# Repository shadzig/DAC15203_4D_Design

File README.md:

# DAC15203: 4D Design

## Virtual pet (Egg)

**Name:** Michail Dzigajev

**Student No:** 96410016

**Course:** BA (Hons) Design & Coding, Level 2.

**Unit Code:** DAC15203

### **Introduction**
Welcome the pet README file. This is an instruction manual on how to start up the pet demo, due to the main scrip currently not being fully functional, and instead I'm showing the visual features of the pet within the demo version that cycles through the sleep mode times and allows you to press the button to reset itself to the smile animation state.

### **Instructions**

##### **Here is how to start up the pet Demo mode**
1. Unfortunately you will have to take off both the top shells of the pet by lightly pulling them away from the base. This is due to me having under-voting issues with the Lithium battery that is in place at the entry of the 3D base hole, so the Pi is no longer powered by the battery temporarily.  I had to remove the wires that connect the battery and Pi while the issue is being resolved, in addition to there being issues of extending the standard power cable to the Pi for which I made an attempt but couldn’t do it safely.

2. Once the shells are off, please plug in the power cable provided with the pet. Make sure to not unplug any of the wires connecting to the shell NeoPixels or button.
3. Place the top shell of the pet over the neoPixel shell and leave it there. 
4. Proceed to powering up the pet by clicking the switch button on the wire.
5. Give the pet a minute or two to boot-up. Once the pet is working the Demo sequence will activate using supervisor.
6. You can then interact with the pet by click on the silver tactile button at the top. Don't be afraid to bush it, as the button is hidden underneath a layer of rubber. 
7. When the button is pressed the pet will revert to the Smile animation state and repeat the process. 
8. Once you are done, simply click on the cable switch again to turn it off.
9. Place the shell in to the grooves one after the other, and firmly secure by pushing down on the shell to slot in with friction.
10. Please refer to the video guide in submitted files if steps above are not clear.

### **Overview**

The pet is running the Demo version due to failure to complete the main script successfully. All individual parts work pet work as shown in one of the videos submitted (Counter, Sound, Button & LEDs). Also, the pet currently does not fully support communication with the web interface server, as I could not accomplish an effective method of transferring data to Mlab where it was stored. 

The interface is operational, and displays the counter mechanism I would use to determine the pets happiness in a form of a percentage gauge, which is split in to the 4 mode categories the pet displays.

I had to remove the wires from the lithium battery and Pi for now, as it could damage the Pi by under-volting the power supply, which is necessary for the components to work. Plus it was a connecting them in the current state pose a safety risk, due to custom wires or connections being needed (the wires were being damaged from being bent).

[**Backup of files on GitHub**](https://github.com/shadzig/DAC15203_4D_Design)

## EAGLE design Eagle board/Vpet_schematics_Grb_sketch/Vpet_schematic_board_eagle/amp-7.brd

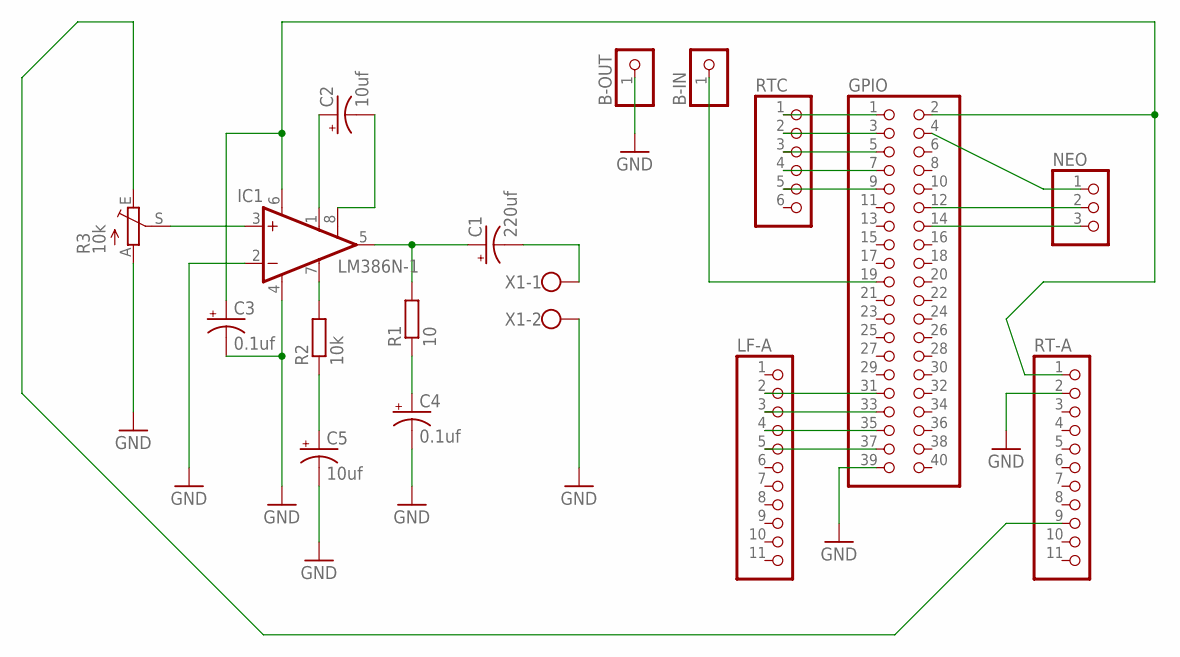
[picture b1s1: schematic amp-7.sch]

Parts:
B-IN: PINHD-1X1; 1X01
B-OUT: PINHD-1X1; 1X01
C1: 220uf; E2-5
C2, C5: 10uf; E2-4
C3, C4: 0.1uf; E2-4
GPIO: PINHD-2X20; 2X20
IC1: LM386N-1; DIL08
LF-A: HEADER-1X1176MIL; 1X11_ROUND_76
NEO: PINHD-1X3; 1X03
R1: 10; 0204/7
R2: 10k; 0204/7
R3: 10k; LI10
RT-A: HEADER-1X1176MIL; 1X11_ROUND_76
RTC: PINHD-1X6; 1X06
X1: W237-102

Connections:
5V: C3.+, GPIO.2, IC1.6 (VS), RT-A.1
AUDIO-DATA: R3.E, RT-A.9
DATA: GPIO.12, NEO.2
GND: B-OUT.1, C3.-, C4.-, C5.-, GPIO.39, IC1.2 (-IN), IC1.4 (GND), R3.A, RT-A.2, X1.2
GND3: GPIO.14, NEO.3
unnamed: IC1.3 (+IN), R3.S
unnamed: C4.+, R1.1
unnamed: IC1.7 (BYPASS), R2.2
unnamed: C2.+, IC1.1 (GAIN)
unnamed: C2.-, IC1.8 (GAIN)
unnamed: C1.+, IC1.5 (OUT), R1.2
unnamed: C1.-, X1.1
unnamed: C5.+, R2.1
unnamed: GPIO.31, LF-A.2
unnamed: GPIO.33, LF-A.3
unnamed: GPIO.35, LF-A.4
unnamed: GPIO.37, LF-A.5
unnamed: GPIO.1, RTC.1
unnamed: GPIO.3, RTC.2
unnamed: B-IN.1, GPIO.19
unnamed: GPIO.5, RTC.3
unnamed: GPIO.7, RTC.4
unnamed: GPIO.9, RTC.5
POWER: GPIO.4, NEO.1

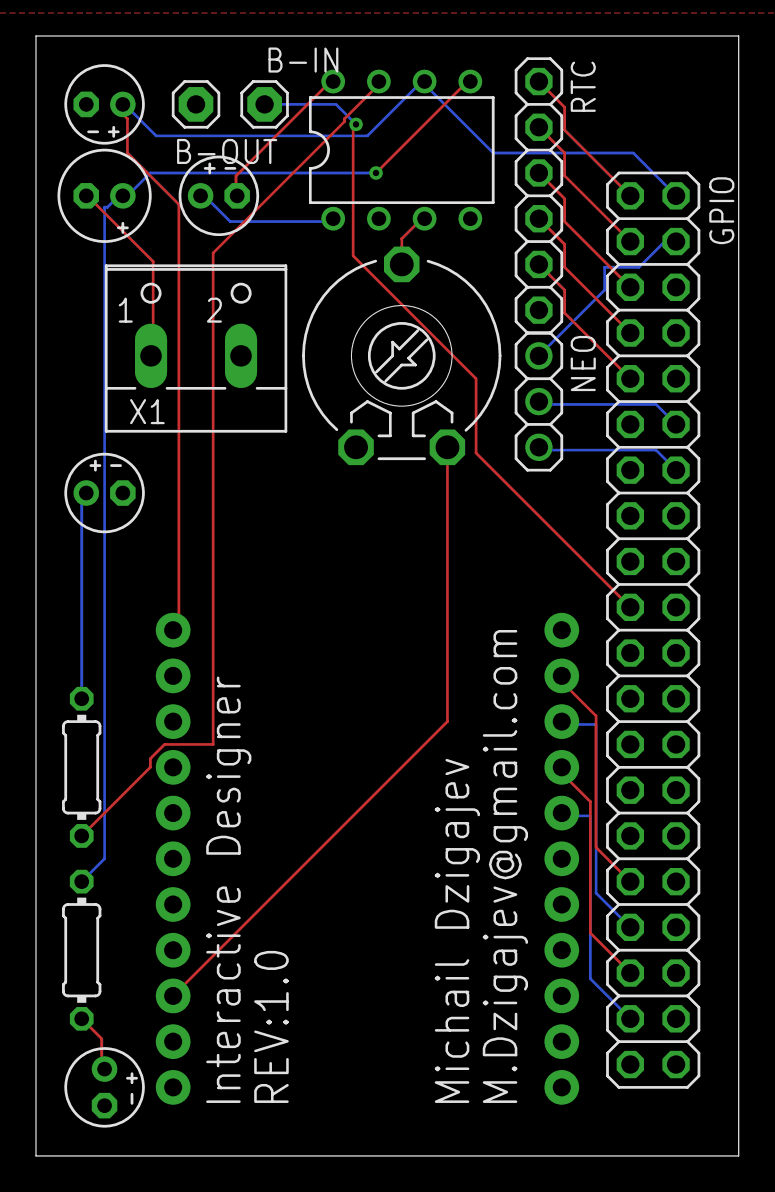
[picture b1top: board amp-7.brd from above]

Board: 2 copper layers, 39.0 x 62.2 mm, 17 parts (0 on the bottom side), 24 nets.

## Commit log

2018-02-21 New content (backup)
    Backup
2018-02-21 Create README.md
    Readme

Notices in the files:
parts and their libraries:
microbuilder: This work is placed in the public domain, and may be freely used for commercial and non-commercial work with the following conditions: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
